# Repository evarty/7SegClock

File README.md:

This code is based on the AVR Atmege328p. The time is kept by a DS1307 RTC. Two button are used to set the hours and minutes. The time is displayed on 4 7-segment displays driven by 74HC595 8-bit shift registers. 
The Makefile uses avr-gcc and assumes that all needed files are present as source code in the same directory as main.c and the Makefile itself.

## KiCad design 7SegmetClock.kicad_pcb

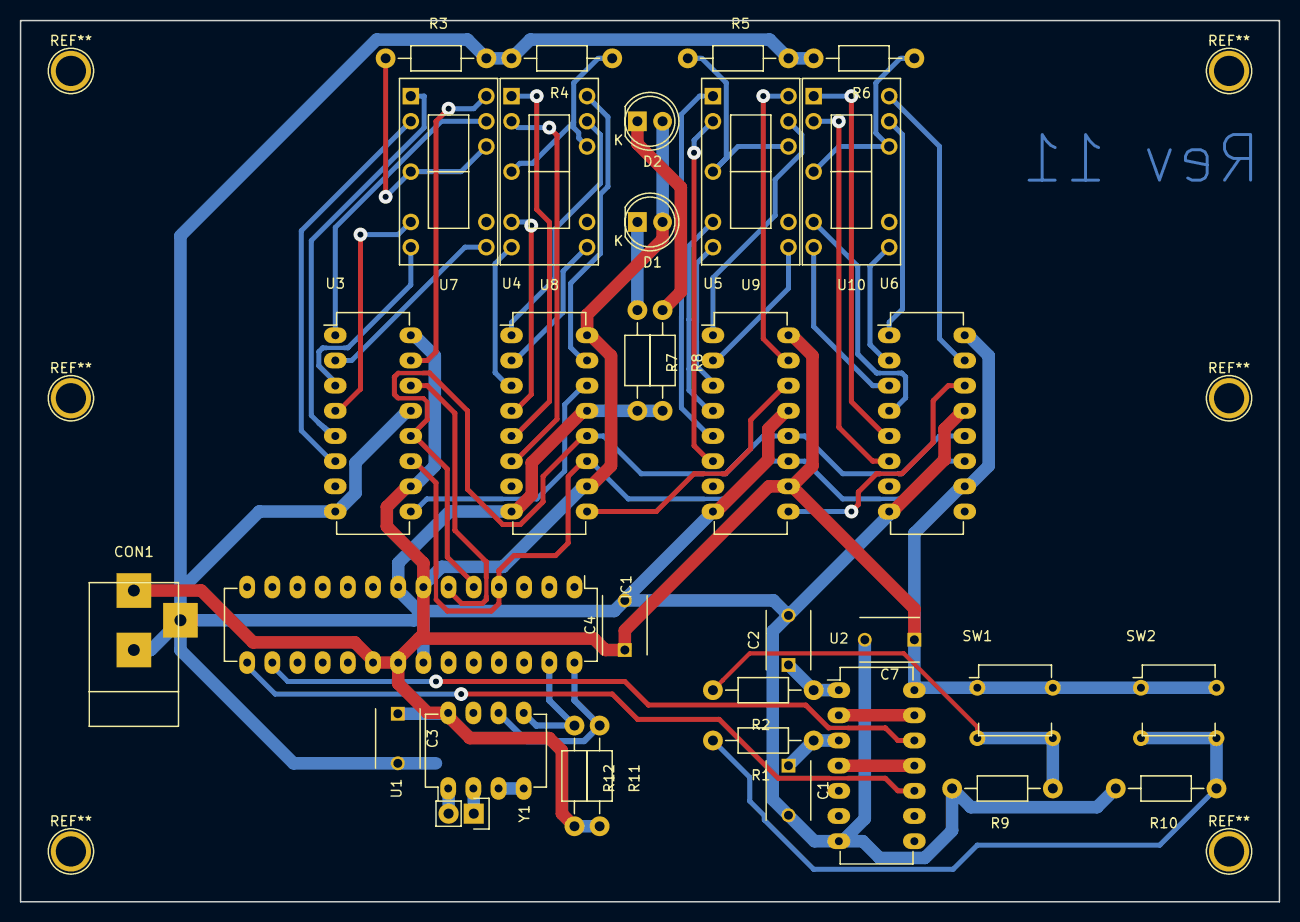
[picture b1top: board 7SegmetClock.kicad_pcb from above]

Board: 2 copper layers, 127.0 x 88.9 mm, 34 parts (0 on the bottom side), 54 nets.

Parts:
C1, C2: .47u; C_Disc_D6_P5
C3, C4, C7: .1u; C_Disc_D6_P5
CON1: BARREL_JACK
D1, D2: LED; LED-5MM
IC1: ATMEGA328P-P; DIP-28_W7.62mm_LongPads
R1, R2, R11, R12: 1k2; Resistor_Horizontal_RM10mm
R3, R4, R5, R6: 1K; Resistor_Horizontal_RM10mm
R7, R8: 470R; Resistor_Horizontal_RM10mm
R9, R10: 10K; Resistor_Horizontal_RM10mm
SW1, SW2: PushButton
U1: DS1307; DIP-8_W7.62mm_LongPads
U2: 74HC14; DIP-14_W7.62mm_LongPads
U3, U4, U5, U6: 74HC595; DIP-16_W7.62mm_LongPads
U7, U8, U9, U10: 7_segment; MAN3640A
Y1: Crystal; Pin_Header_Straight_1x02

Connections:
+5V: C3.1, C4.1, C7.1, CON1.1, D1.2, D2.2, IC1.7, IC1.20, IC1.21, R11.2, R12.2, SW1.1, SW1.4, SW2.1, SW2.4, U1.8, U2.14, U3.10, U3.16, U4.10, U4.16, U5.10, U5.16, U6.10, U6.16
Clock: IC1.4, U3.11, U4.11, U5.11, U6.11
GND: C1.2, C2.2, C3.2, C4.2, C7.2, CON1.2, CON1.3, IC1.8, IC1.22, R3.2, R4.2, R5.2, R6.2, R7.2, R8.2, R9.2, R10.2, U1.3, U1.4, U2.7, U3.8, U3.13, U4.8, U4.13, U5.8, U5.13, U6.8, U6.13
HourButton: R2.2, R9.1, SW1.2, SW1.3
Latch: IC1.5, U3.12, U4.12, U5.12, U6.12
MinuteButton: R1.2, R10.1, SW2.2, SW2.3
unnamed: C1.1, R1.1, U2.3
unnamed: C2.1, R2.1, U2.1
unnamed: D1.1, R7.1
unnamed: D2.1, R8.1
unnamed: IC1.15, U2.10
unnamed: IC1.16, U2.12
unnamed: IC1.27, R12.1, U1.5
unnamed: IC1.28, R11.1, U1.6
unnamed: R3.1, U7.4, U7.12
unnamed: R4.1, U8.4, U8.12
unnamed: R5.1, U9.4, U9.12
unnamed: R6.1, U10.4, U10.12
unnamed: U1.1, Y1.2
unnamed: U1.2, Y1.1
unnamed: U2.4, U2.11
unnamed: U2.2, U2.13
unnamed: U3.1, U7.13
unnamed: U3.2, U7.8
unnamed: U3.3, U7.7
unnamed: U3.4, U7.6
unnamed: U3.5, U7.1
unnamed: U3.6, U7.2
unnamed: U3.9, U4.14
unnamed: U3.15, U7.14
unnamed: U4.1, U8.13
unnamed: U4.2, U8.8
unnamed: U4.3, U8.7
unnamed: U4.4, U8.6
unnamed: U4.5, U8.1
unnamed: U4.6, U8.2
unnamed: U4.9, U5.14
unnamed: U4.15, U8.14
unnamed: U5.1, U9.13
unnamed: U5.2, U9.8
unnamed: U5.3, U9.7
unnamed: U5.4, U9.6
unnamed: U5.5, U9.1
unnamed: U5.6, U9.2
unnamed: U5.9, U6.14
unnamed: U5.15, U9.14
unnamed: U6.5, U10.1
unnamed: U6.6, U10.2
unnamed: U6.4, U10.6
unnamed: U6.3, U10.7
unnamed: U6.2, U10.8
unnamed: U6.1, U10.13
unnamed: U6.15, U10.14
SER: IC1.6, U3.14

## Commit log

2016-04-20 Adding PCB
2016-04-22 added KiCadFiles
2016-04-22 added gerbers
2016-04-22 moved the board files to a new directory
2016-04-22 moved filename
2016-04-22 added needed files
2016-04-22 added pdf schematic
2016-04-23 removed unused library
2016-04-23 removed reference to unused lib
2016-04-23 added comments
2016-04-25 fixed stupid error
2016-04-25 undid really stupid error
2016-04-27 added some comments
